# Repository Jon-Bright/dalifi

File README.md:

# DaliFi
ESP8266-based PCB and code for WiFi communication with DALI-based devices. DALI is standardized as IEC 62386-102.

This project consists of three parts:

* hardware: Design for a fairly simple through-hole PCB capable of powering a bus, sending and receiving messages to/from DALI-compliant lamps. Design done using EAGLE, Gerber files included.
* library: An Arduino library for communicating with DALI-compliant lamps.
* example: An example Arduino application using the library and providing a WiFi-based interface to control attached lamps.

Each of these is covered in more detail below.

## Hardware

KNOWN BUG: the silkscreen for T2 is incorrect, at least for the 2N2222s I have.

The hardware can be broadly separated into seven parts:

* Mains voltage to 12v conversion.
  * This is done by a self-contained RAC05-12SK unit.
  * The resulting 12v is used to (optionally, see below) power the bus to the lamps, as well as the board itself.
* 12v to 3.3v conversion.
  * Another self-contained unit, RNM-123.3S.
  * The 3.3v is used to power the ESP8266.
* Bus power: this takes the 12v from above and limits its current as well as making it short-tolerant.
  * DALI communication involves frequent shorts of the bus (it's how "low" is communicated).
  * As more power is drawn on the bus (including when it's shorted), the voltage across R2 increases.
  * When the power drawn reaches 144mA, that's a voltage across R2 of 1.44V - and that's equivalent to the forward voltage of the two diodes. Current begins to flow through them.
  * The current flow across the two diodes means the transistor gradually turns off.
  * The current through the diodes is limited by R1, to about 12mA.
  * There are two jumpers after all of this. If something else is powering the bus, disconnect the jumpers and this circuit won't.
* DALI polarity protection.
  * If we're powering the bus, this isn't needed - we know which polarity is in use. But if we're not, then the bus can be either polarity. This rectifier deals with this and gives us plus and minus.
* DALI input.
  * When the DALI+ voltage is high enough (~5.6V) above DALI-, the Zener diode (D3) starts conducting.
  * This causes the LED in optoisolator OK1 to light.
  * R3 limits current across D3 (and through OK1).
  * When the LED in OK1 is active, DALI_I (which is otherwise pulled high by R5) is pulled low by OK1.
* DALI output.
  * When DALI_O is high, the LED in OK2 is active.  (R7 limits current through OK2 and current sourced from the ESP8266.)
  * This in turn causes current to flow to the base of T2 (via current-limiter R4). T2's base is otherwise pulled low by R6.
  * This causes T2 to short DALI+ and DALI-.  (A 2N2222 is good for 600mA continuous current and the DALI bus should be at most 250mA.)
* The ESP8266.
  * We're expecting a board with USB connector and so forth, as opposed to a blank ESP8266.

I am _not_ a hardware engineer. People who are will probably take one look at the design and go cry into pillows. Improvements are very welcome.

## Library

The library:

* Includes metadata for all opcodes (and "opcode addresses" like DAPC, DTR0) in the standard.
* Only implements functions to send a limited subset of those opcodes.
* Implementation of additional opcodes should be trivial.
* Includes functions for assigning short addresses to lamps.
* Handles all aspects of encoding and decoding the Manchester encoding used by devices.
* Is designed to work with the PCB above
  * Any PCB featuring an ESP8266 with two pins assigned to input from and output to DALI-compliant lamps should work, though.
  * If using a different PCB with differently-performing hardware, the timing definitions for half-bits at the top of dali.cpp might need tweaking.

## Example

The example Arduino application uses the library.  It features:

* Saving of WiFi connection using the ESP8266's (fake) EEPROM functionality.
* An Access Point function when no WiFi connection info is saved, to collect and save the information.
* A simple text-based interface for controlling the lamps.
* Commands for controlling lamps and querying their status.

My intention is to add MQTT support in addition to (or in place of) the simple text-based interface.

## Testing

I've tested this with three DALI-compliant lamps in my possession (two from the same manufacturer). It works fine with all of them. I've had it in operation with two of those lamps for a total of ~5 years of runtime without problems. Nevertheless, see the disclaimer of all warranty below.

## Legal

DALI, the DALI Logo, DALI-2, the DALI-2 Logo, DiiA, the DiiA Logo, D4i, the D4i Logo, DALI+ and the DALI+ Logo are trademarks in various countries in the exclusive use of the Digital Illumination Interface Alliance. No claim is made to any of these marks, nor is it claimed that this work is compliant with standards issued by the Alliance.

Absolutely no warranty is given for any element of this work. If it breaks, you get to keep both pieces. If it breaks your lamp(s), same. See the warranty exclusion in LICENSE.

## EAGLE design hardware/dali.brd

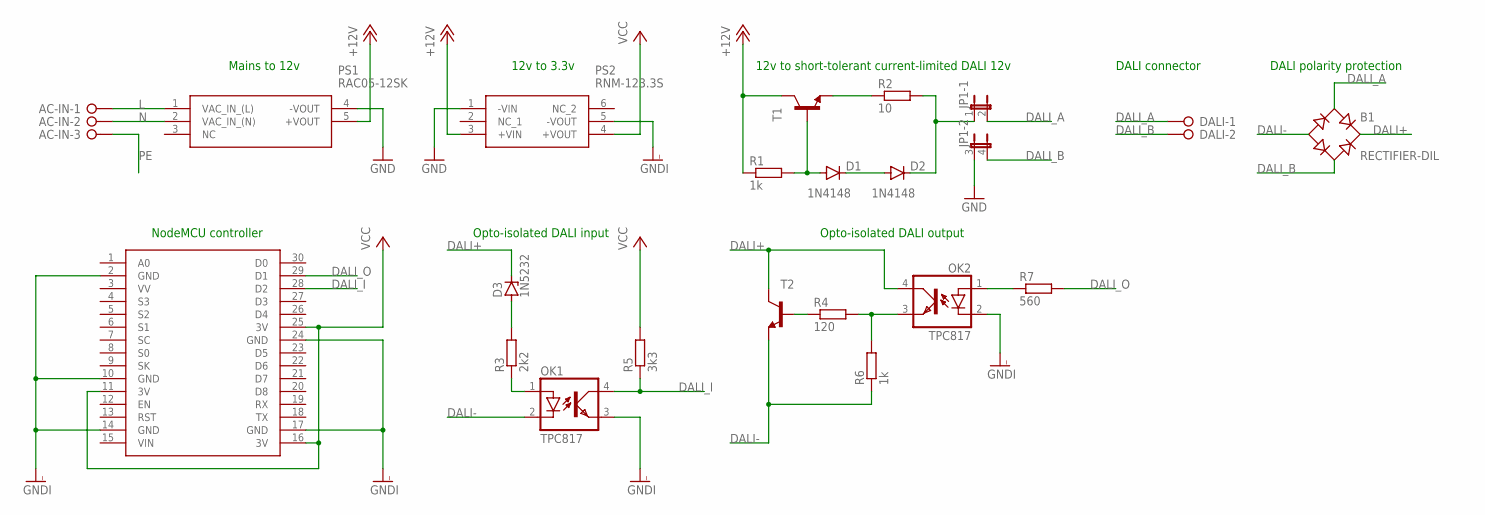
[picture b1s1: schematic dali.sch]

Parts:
AC-IN: 39544-3003
B1: RECTIFIER-DIL; B-DIL
D1, D2: 1N4148; DO35-10
D3: 1N5232; DO35Z10
DALI: 39544-3002
JP1: JP2QE; JP2Q
OK1, OK2: TPC817; DIL04
PS1: RAC05-12SK
PS2: RNM-123.3S; DIP508W115P254L830H705Q6N
R1, R6: 1k; 0207/7
R2: 10; 0207/7
R3: 2k2; 0207/7
R4: 120; 0207/7
R5: 3k3; 0207/7
R7: 560; 0207/7
T1, T2: MPS2222A-NPN-TO92-CBE; TO92-CBE
U$1: NODEMCU

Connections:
+12V: PS1.5 (+VOUT), PS2.3 (+VIN), R1.1, T1.C
DALI+: B1.+, D3.C, OK2.4 (COL), T2.C
DALI-: B1.-, OK1.2 (C), R6.1, T2.E
DALI_A: B1.AC1, DALI.1, JP1.2
DALI_B: B1.AC2, DALI.2, JP1.4 (2)
DALI_I: OK1.4 (COL), R5.1, U$1.28 (D2)
DALI_O: R7.2, U$1.29 (D1)
GND: JP1.3 (1), PS1.4 (-VOUT), PS2.1 (-VIN)
GNDI: OK1.3 (EMIT), OK2.2 (C), PS2.5 (-VOUT), U$1.2 (GND), U$1.10 (GND), U$1.14 (GND), U$1.17 (GND), U$1.24 (GND)
L: AC-IN.1, PS1.1 (VAC_IN_(L))
N: AC-IN.2, PS1.2 (VAC_IN_(N))
unnamed: D1.A, R1.2, T1.B
unnamed: D1.C, D2.A
unnamed: R2.1, T1.E
unnamed: D3.A, R3.2
unnamed: OK1.1 (A), R3.1
unnamed: R4.1, T2.B
unnamed: OK2.3 (EMIT), R4.2, R6.2
unnamed: OK2.1 (A), R7.1
unnamed: D2.C, JP1.1, R2.2
PE: AC-IN.3
VCC: PS2.4 (+VOUT), R5.2, U$1.11 (3V), U$1.16 (3V), U$1.25 (3V)

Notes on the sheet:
Mains to 12v
12v to 3.3v
12v to short-tolerant current-limited DALI 12v
NodeMCU controller
DALI connector
DALI polarity protection
Opto-isolated DALI input
Opto-isolated DALI output

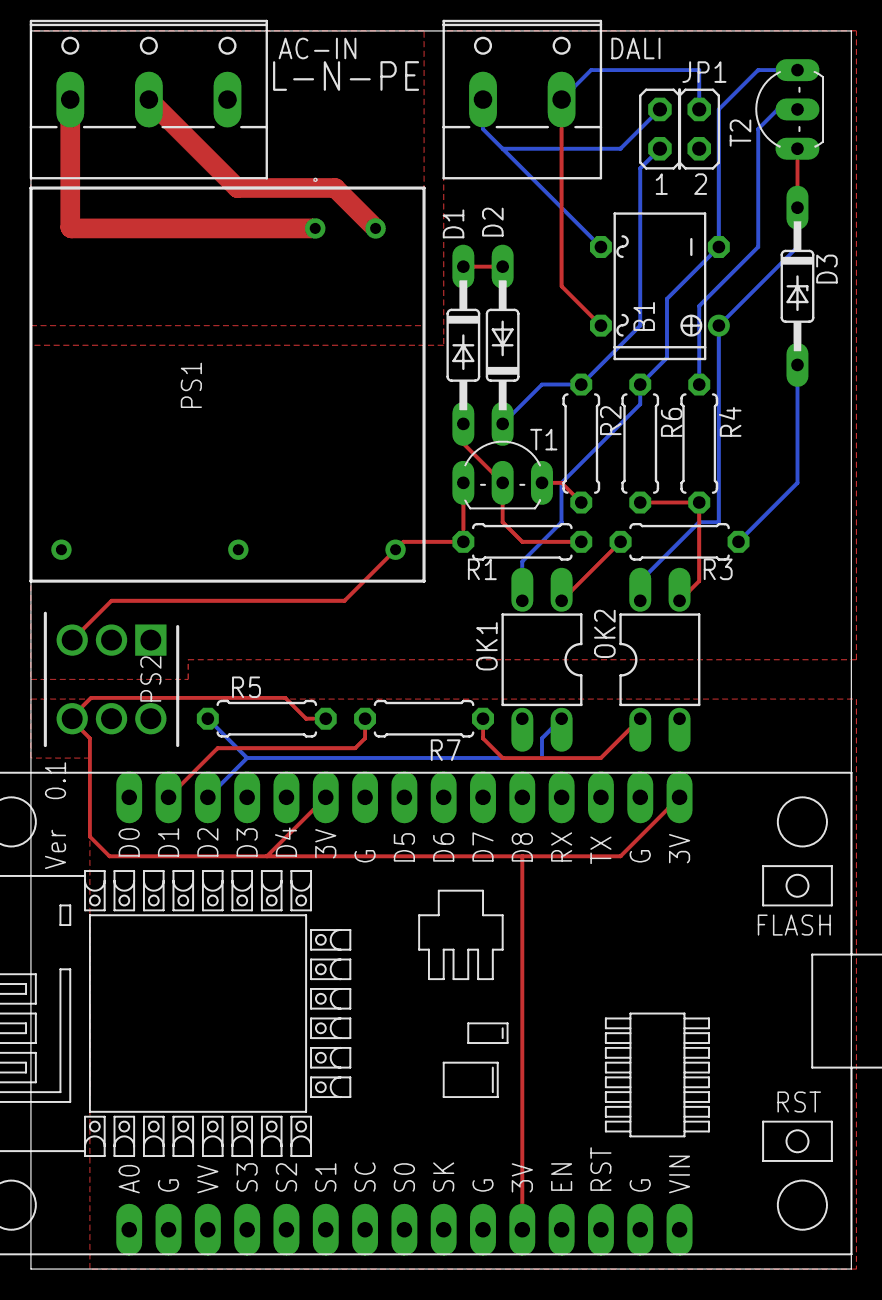
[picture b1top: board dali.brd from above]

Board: 2 copper layers, 53.0 x 80.0 mm, 21 parts (0 on the bottom side), 21 nets.

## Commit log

2022-06-18 First released version of the project. Full details in README.md.
2022-06-18 Actually use the EEPROM functionality rather than RTC memory. I'd understood these to be two APIs to the same place, but that's not the case - and RTC memory may not survive a power cycle.
2023-03-04 Properly support self-addressed lamps.
    In sent commands, the bottom bit of the address byte determines whether this
    is a DAPC (Direct Arc Power Control) command or not. If the bit is zero, it's
    a DAPC command, otherwise it's not.
    We were previously dealing with this by, in reAddressLamps, setting the bottom
    bit and in sendDapc, clearing it. This worked fine if using reAddressLamps, but
    was broken if someone was addressing their own lamps.
